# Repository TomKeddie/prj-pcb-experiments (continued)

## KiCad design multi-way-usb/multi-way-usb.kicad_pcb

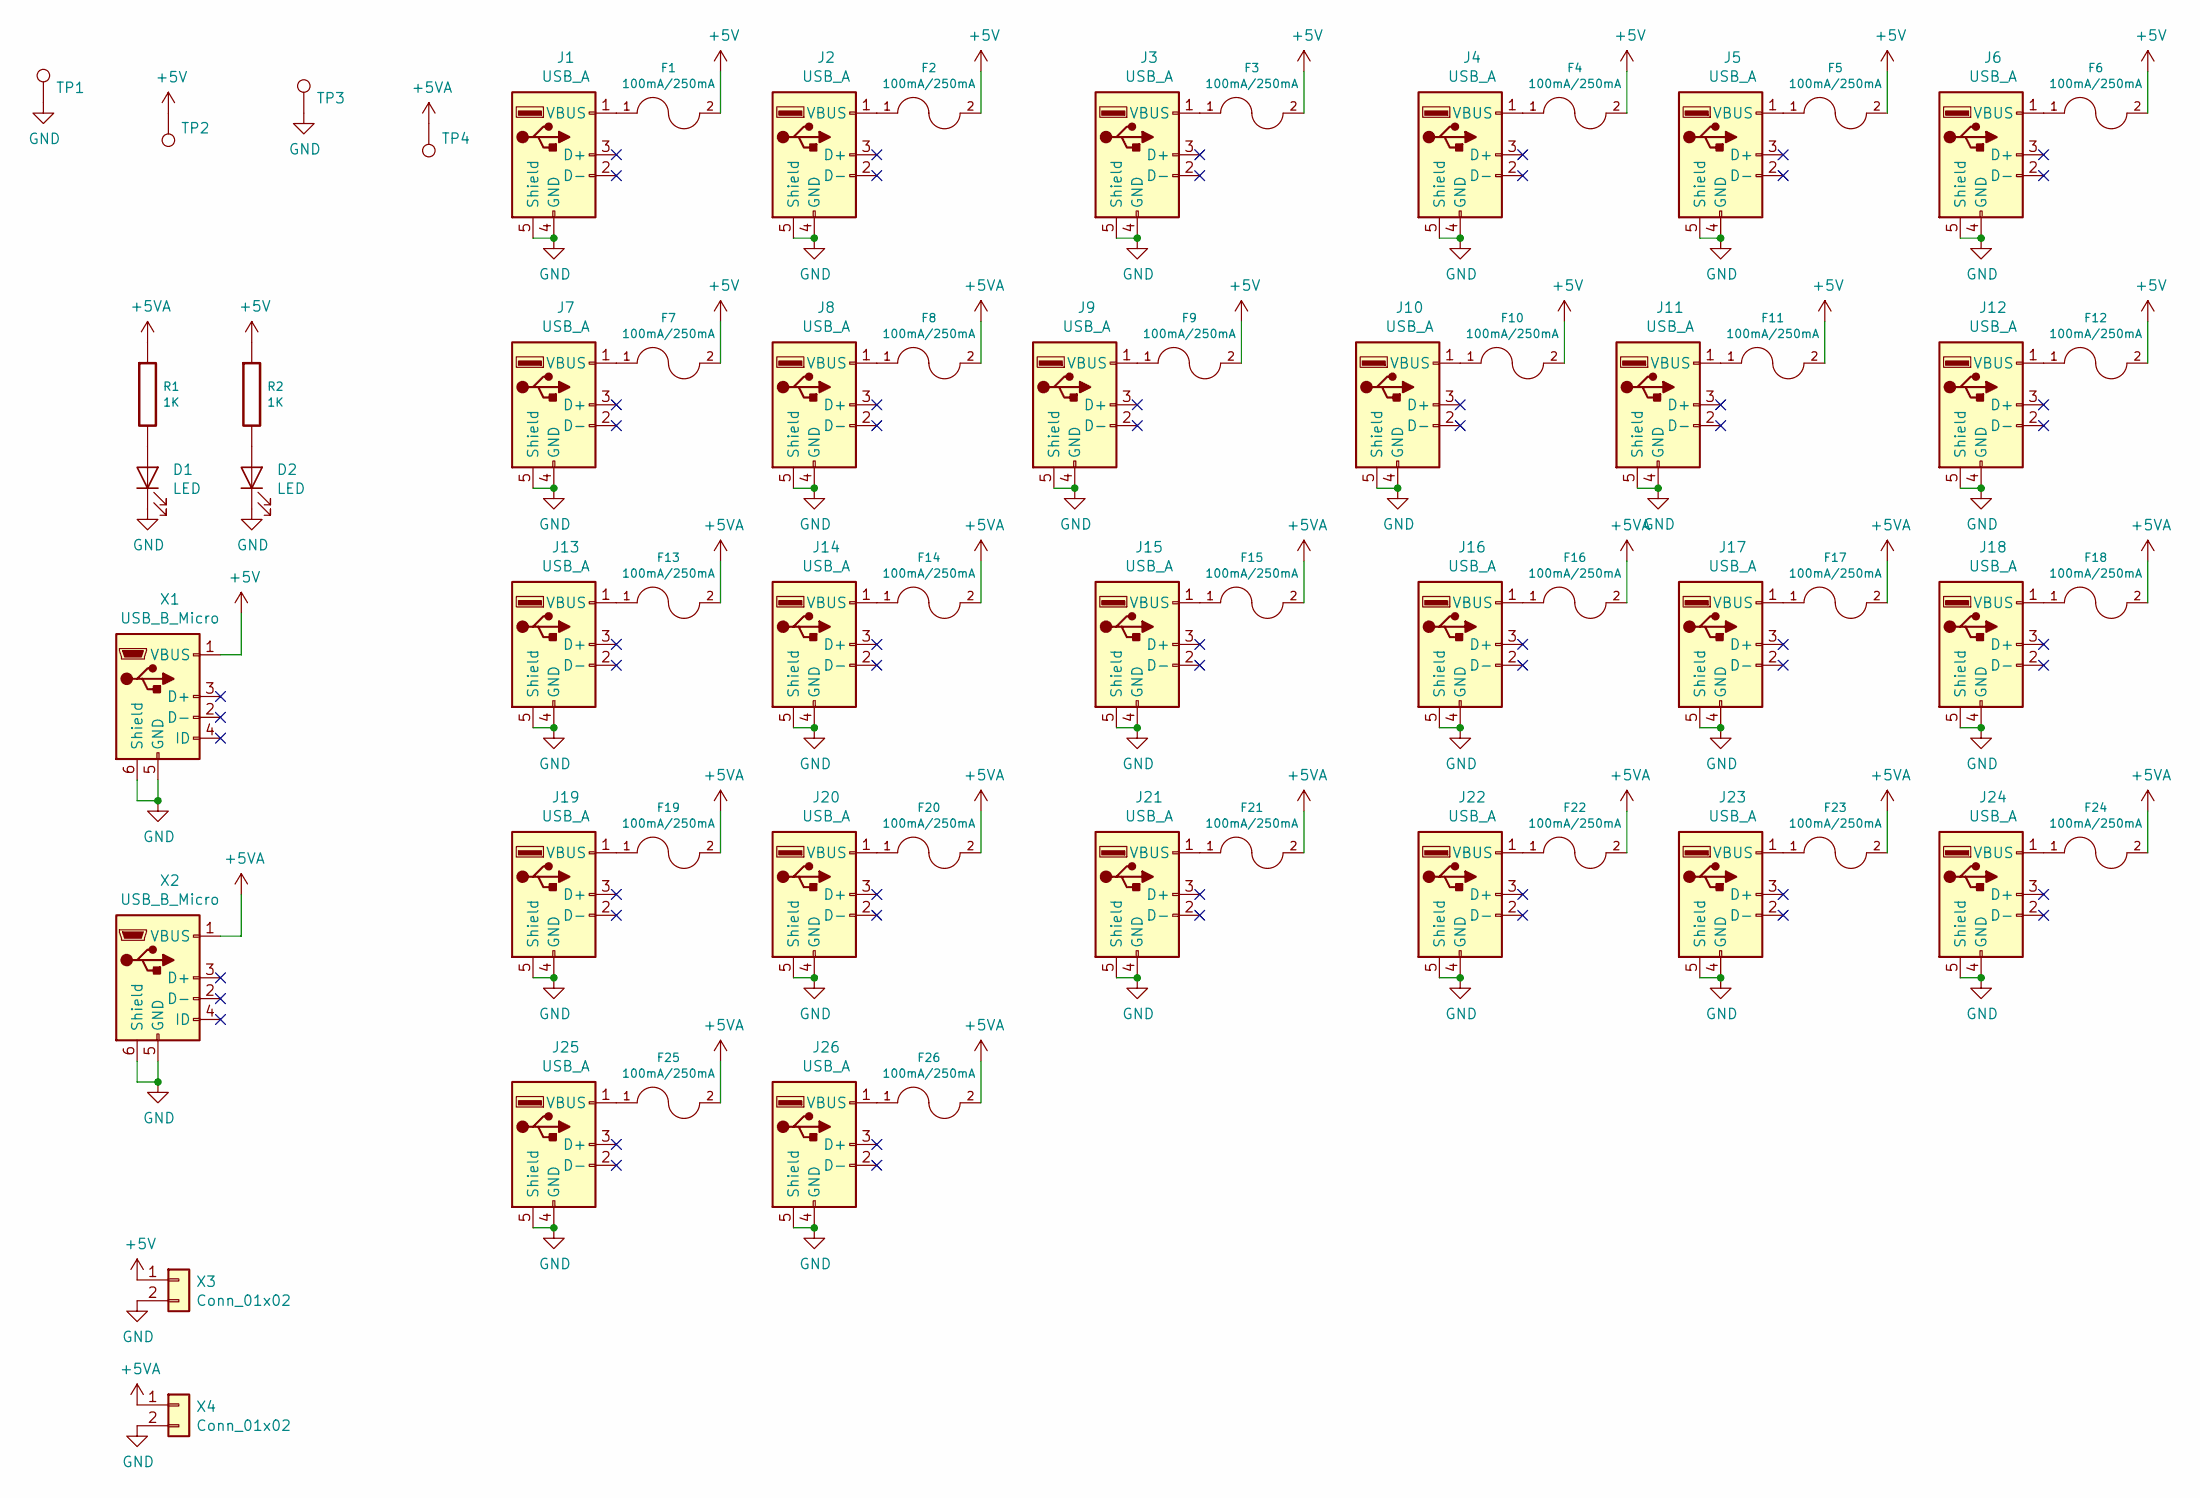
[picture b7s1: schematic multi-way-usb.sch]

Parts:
D1, D2: LED; LED_0805_2012Metric
F1, F2, F3, F4, F5, F6, F7, F8, F9, F10, F11, F12, F13, F14, F15, F16, F17, F18, F19, F20, F21, F22, F23, F24, F25, F26: 100mA/250mA; C_1206_3216Metric; LCSC C20981
J1, J2, J3, J4, J5, J6, J10, J11, J12, J13, J14: USB_A; OST_USB-A1HSW6-INVERTED; LCSC C42642
J7, J8, J9, J15, J16, J17: USB_A; CUI_UJ2-AV-1-TH; LCSC C42642
J18, J19, J20, J21, J22, J23, J24, J25, J26: USB_A; CUI_UJ2-AV-1-TH; Digikey 102-3995-ND
R1, R2: 1K; C_0805_2012Metric; LCSC C17513
TP1, TP3: GND; TestPoint_Pad_D3.0mm
TP2, TP4: 5V; TestPoint_Pad_D3.0mm
X1, X2: USB_B_Micro; USB_MICRO_TAOBAO_SMD_PTH
X3, X4: Conn_01x02; PinHeader_1x02_P2.54mm_Vertical

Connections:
+5V: F1.2, F2.2, F3.2, F4.2, F5.2, F6.2, F7.2, F9.2, F10.2, F11.2, F12.2, R2.1, TP2.1, X1.1 (VBUS), X3.1
+5VA: F8.2, F13.2, F14.2, F15.2, F16.2, F17.2, F18.2, F19.2, F20.2, F21.2, F22.2, F23.2, F24.2, F25.2, F26.2, R1.1, TP4.1, X2.1 (VBUS), X4.1
GND: D1.1 (K), D2.1 (K), J1.4 (GND), J1.5 (Shield), J2.4 (GND), J2.5 (Shield), J3.4 (GND), J3.5 (Shield), J4.4 (GND), J4.5 (Shield), J5.4 (GND), J5.5 (Shield), J6.4 (GND), J6.5 (Shield), J7.4 (GND), J7.5 (Shield), J8.4 (GND), J8.5 (Shield), J9.4 (GND), J9.5 (Shield), J10.4 (GND), J10.5 (Shield), J11.4 (GND), J11.5 (Shield), J12.4 (GND), J12.5 (Shield), J13.4 (GND), J13.5 (Shield), J14.4 (GND), J14.5 (Shield), J15.4 (GND), J15.5 (Shield), J16.4 (GND), J16.5 (Shield), J17.4 (GND), J17.5 (Shield), J18.4 (GND), J18.5 (Shield), J19.4 (GND), J19.5 (Shield), J20.4 (GND), J20.5 (Shield), J21.4 (GND), J21.5 (Shield), J22.4 (GND), J22.5 (Shield), J23.4 (GND), J23.5 (Shield), J24.4 (GND), J24.5 (Shield), J25.4 (GND), J25.5 (Shield), J26.4 (GND), J26.5 (Shield), TP1.1, TP3.1, X1.5 (GND), X1.6 (Shield), X2.5 (GND), X2.6 (Shield), X3.2, X4.2
unnamed: D1.2 (A), R1.2
unnamed: D2.2 (A), R2.2
unnamed: F1.1, J1.1 (VBUS)
unnamed: F2.1, J2.1 (VBUS)
unnamed: F3.1, J3.1 (VBUS)
unnamed: F4.1, J4.1 (VBUS)
unnamed: F5.1, J5.1 (VBUS)
unnamed: F6.1, J6.1 (VBUS)
unnamed: F7.1, J7.1 (VBUS)
unnamed: F8.1, J8.1 (VBUS)
unnamed: F9.1, J9.1 (VBUS)
unnamed: F10.1, J10.1 (VBUS)
unnamed: F11.1, J11.1 (VBUS)
unnamed: F12.1, J12.1 (VBUS)
unnamed: F13.1, J13.1 (VBUS)
unnamed: F14.1, J14.1 (VBUS)
unnamed: F15.1, J15.1 (VBUS)
unnamed: F16.1, J16.1 (VBUS)
unnamed: F17.1, J17.1 (VBUS)
unnamed: F18.1, J18.1 (VBUS)
unnamed: F19.1, J19.1 (VBUS)
unnamed: F20.1, J20.1 (VBUS)
unnamed: F21.1, J21.1 (VBUS)
unnamed: F22.1, J22.1 (VBUS)
unnamed: F23.1, J23.1 (VBUS)
unnamed: F24.1, J24.1 (VBUS)
unnamed: F25.1, J25.1 (VBUS)
unnamed: F26.1, J26.1 (VBUS)

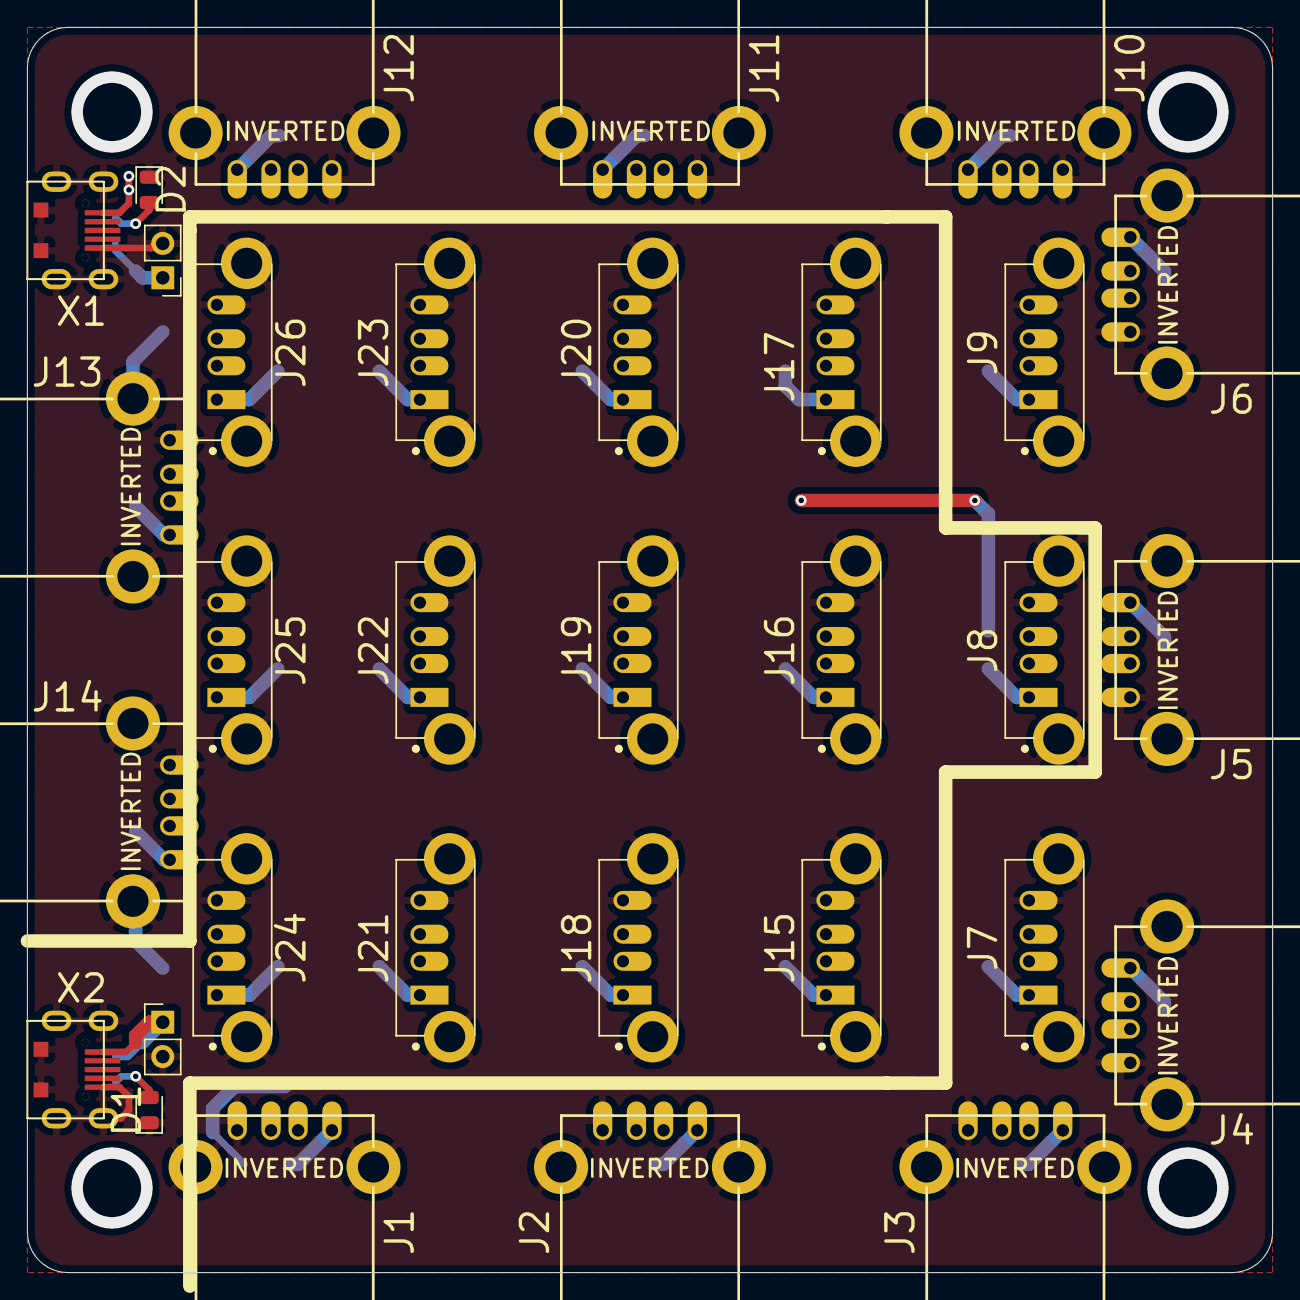
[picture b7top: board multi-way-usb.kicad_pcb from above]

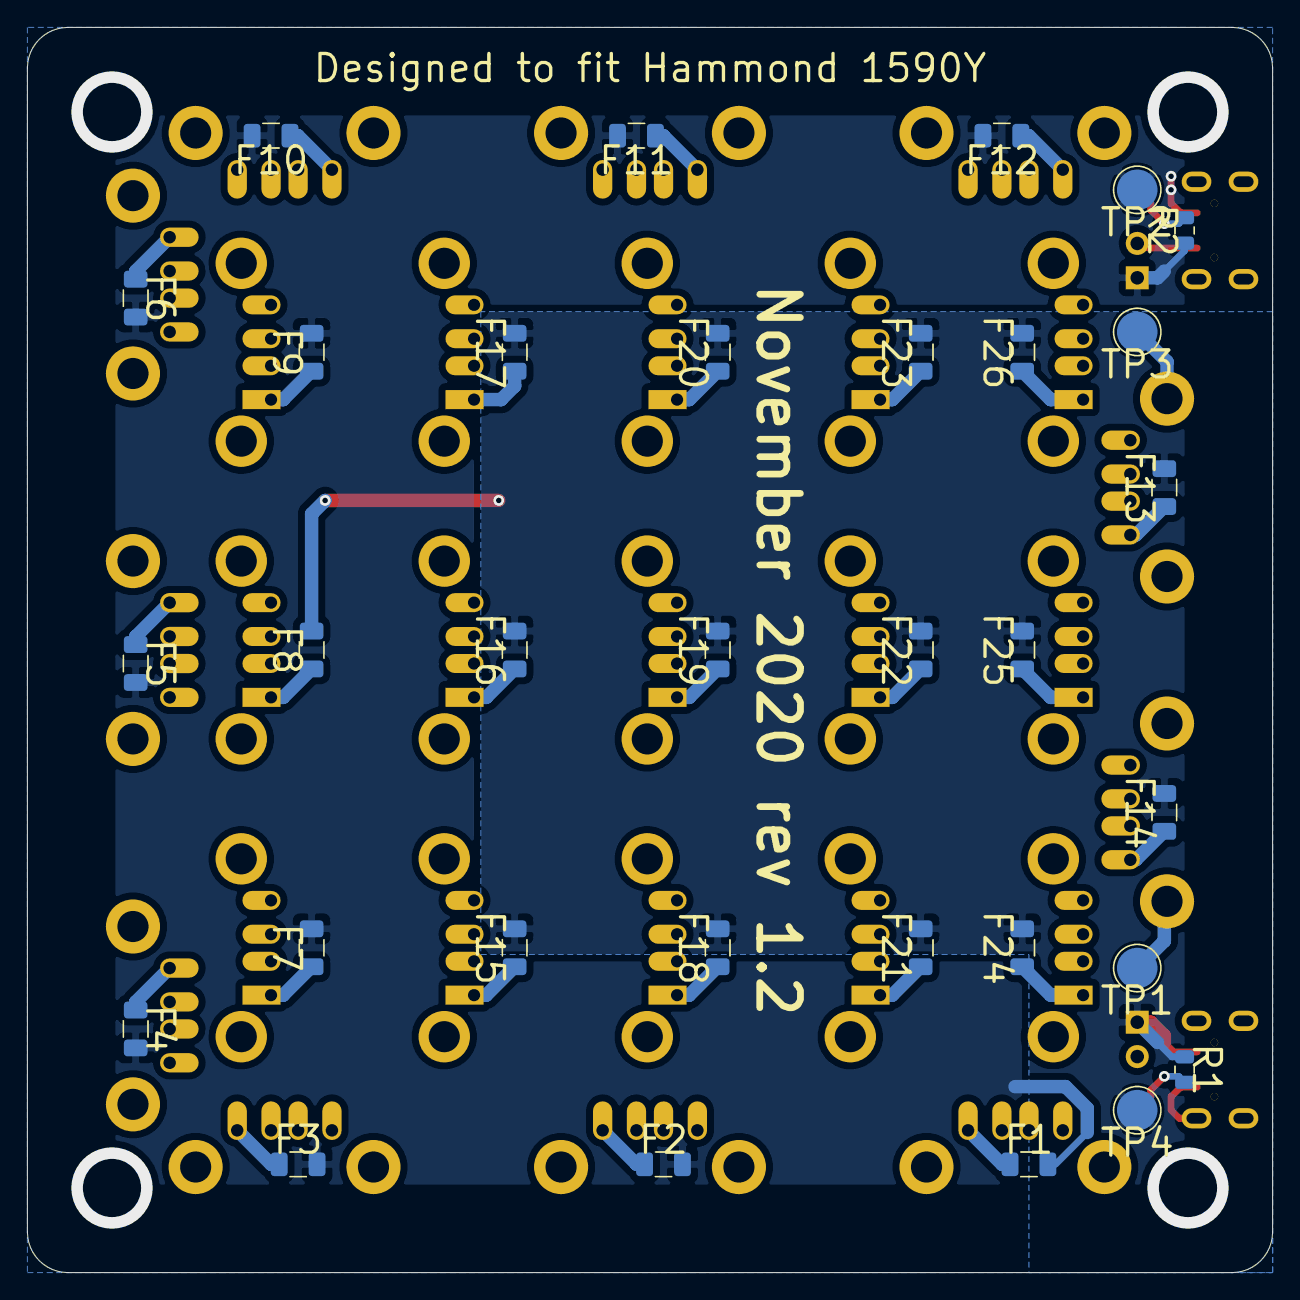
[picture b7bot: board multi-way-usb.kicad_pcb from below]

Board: 2 copper layers, 92.0 x 92.0 mm, 64 parts (32 on the bottom side), 31 nets.
